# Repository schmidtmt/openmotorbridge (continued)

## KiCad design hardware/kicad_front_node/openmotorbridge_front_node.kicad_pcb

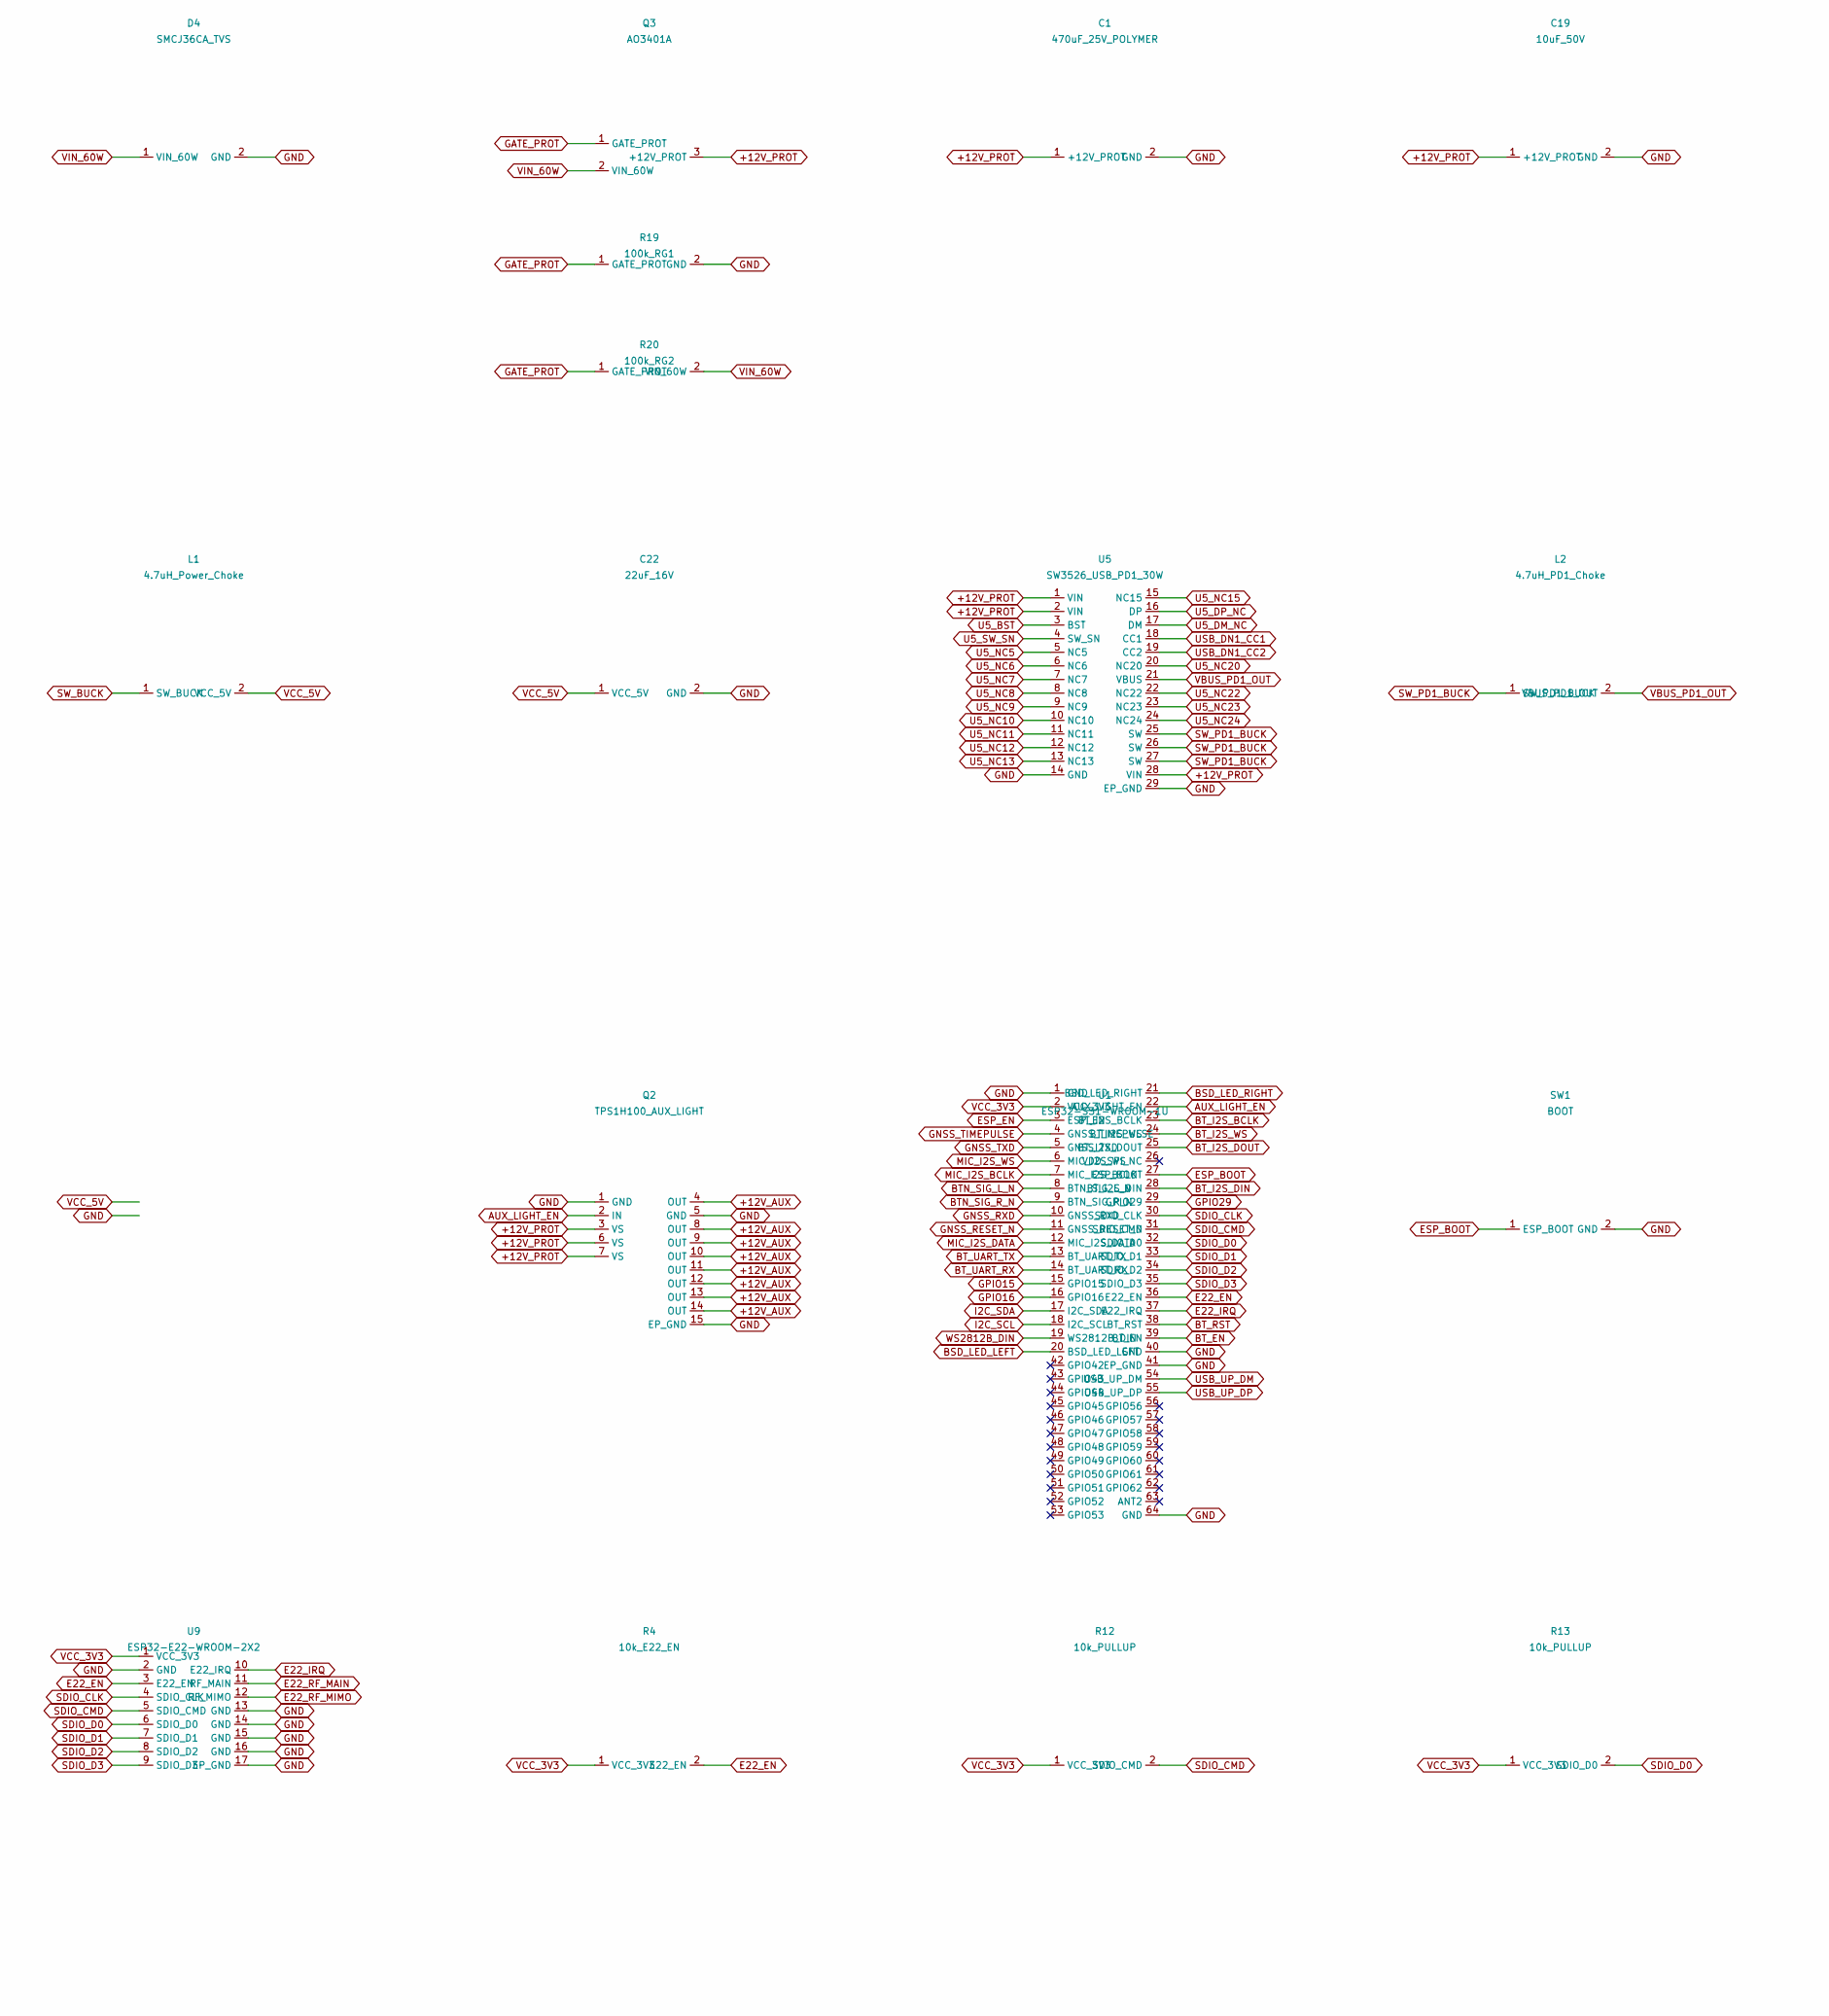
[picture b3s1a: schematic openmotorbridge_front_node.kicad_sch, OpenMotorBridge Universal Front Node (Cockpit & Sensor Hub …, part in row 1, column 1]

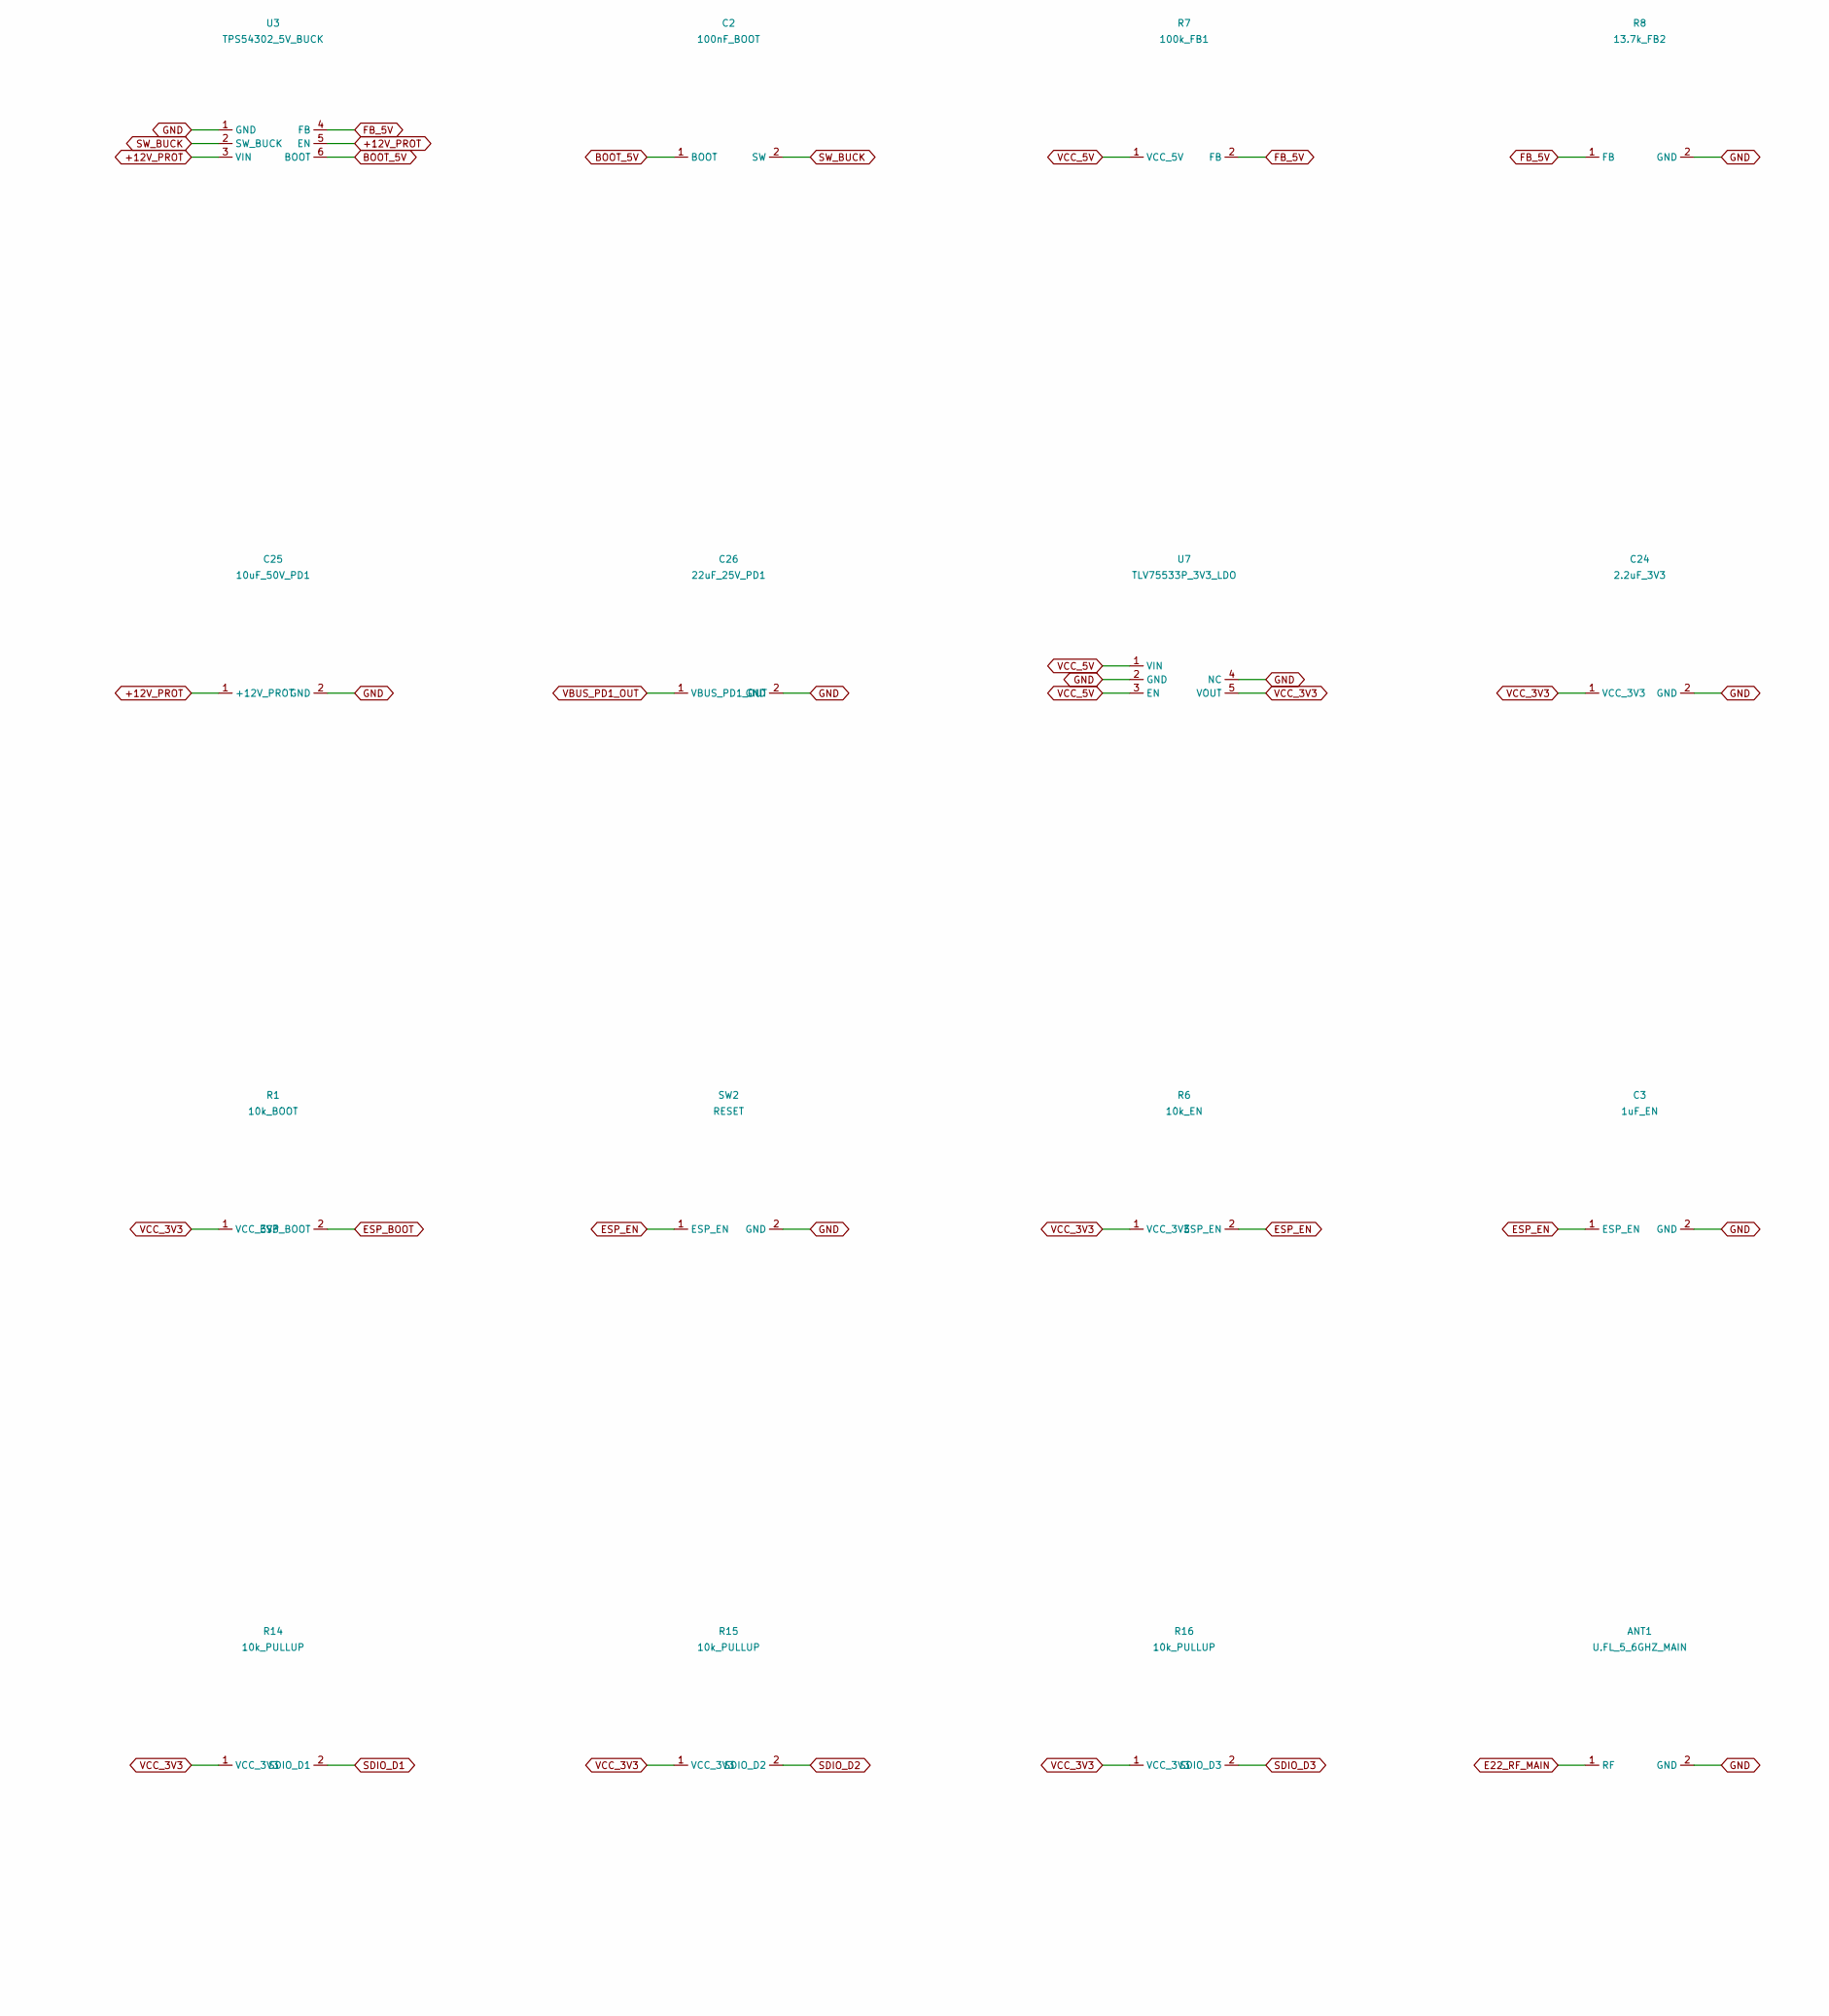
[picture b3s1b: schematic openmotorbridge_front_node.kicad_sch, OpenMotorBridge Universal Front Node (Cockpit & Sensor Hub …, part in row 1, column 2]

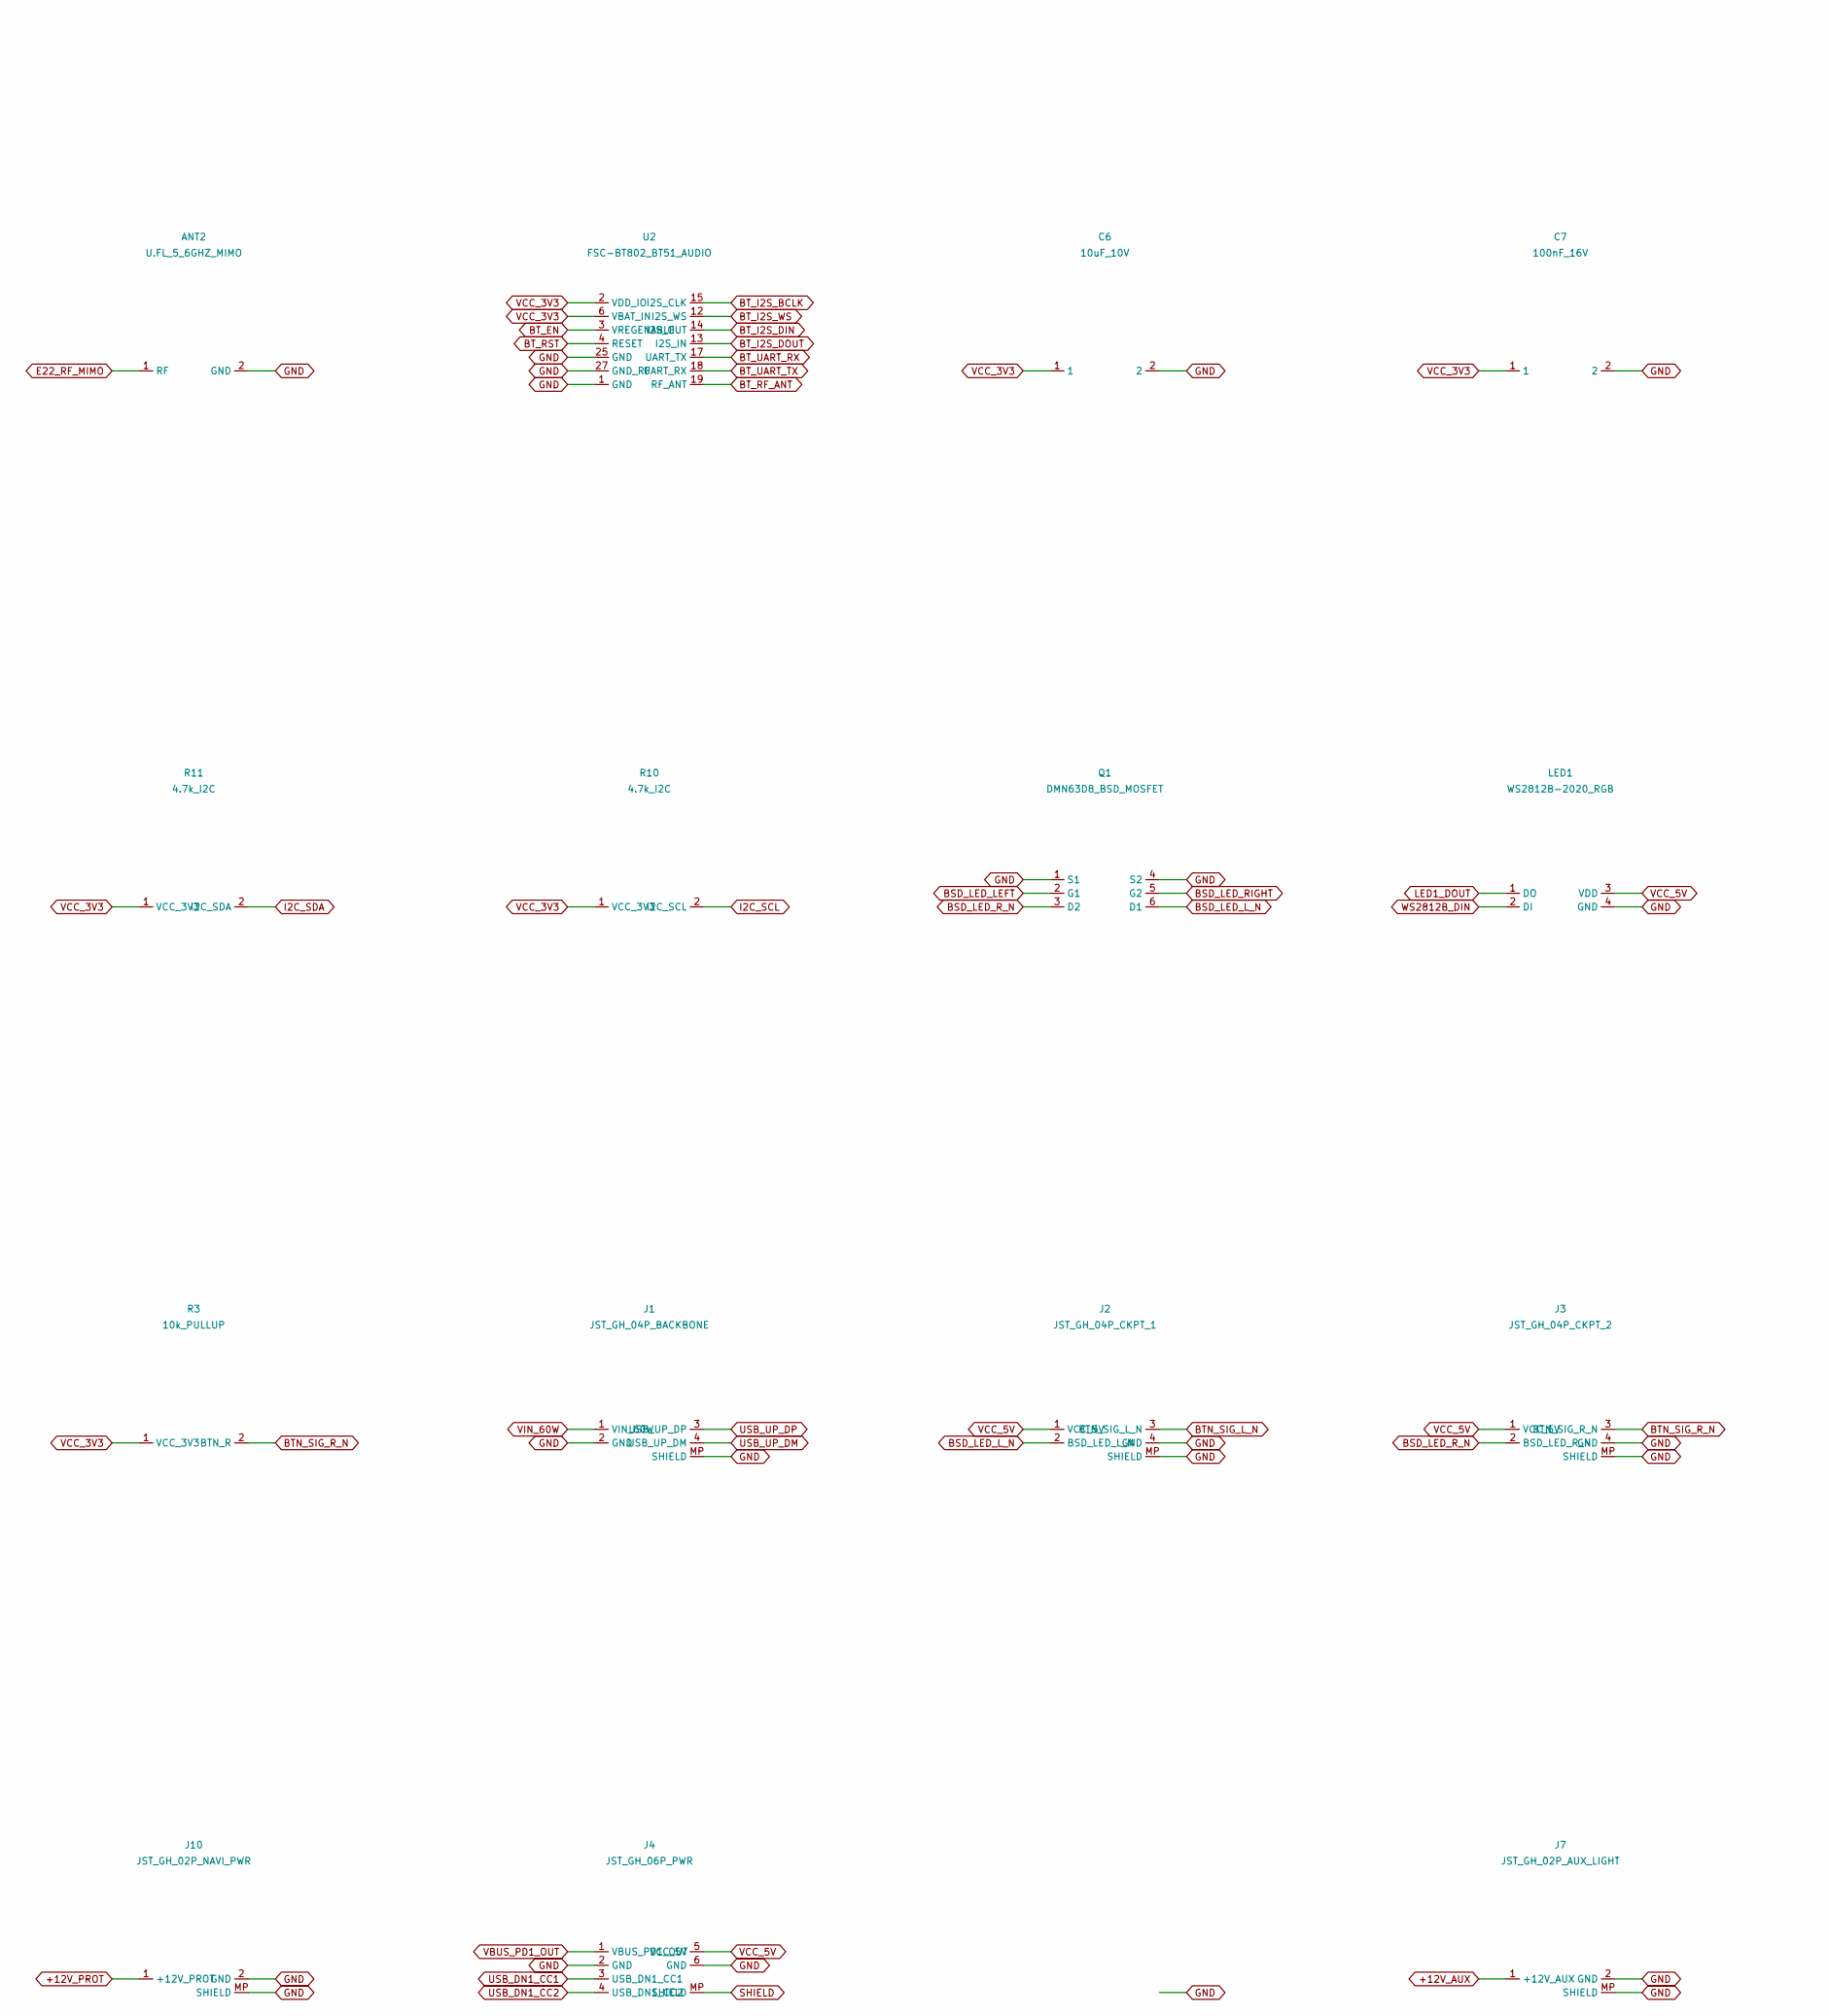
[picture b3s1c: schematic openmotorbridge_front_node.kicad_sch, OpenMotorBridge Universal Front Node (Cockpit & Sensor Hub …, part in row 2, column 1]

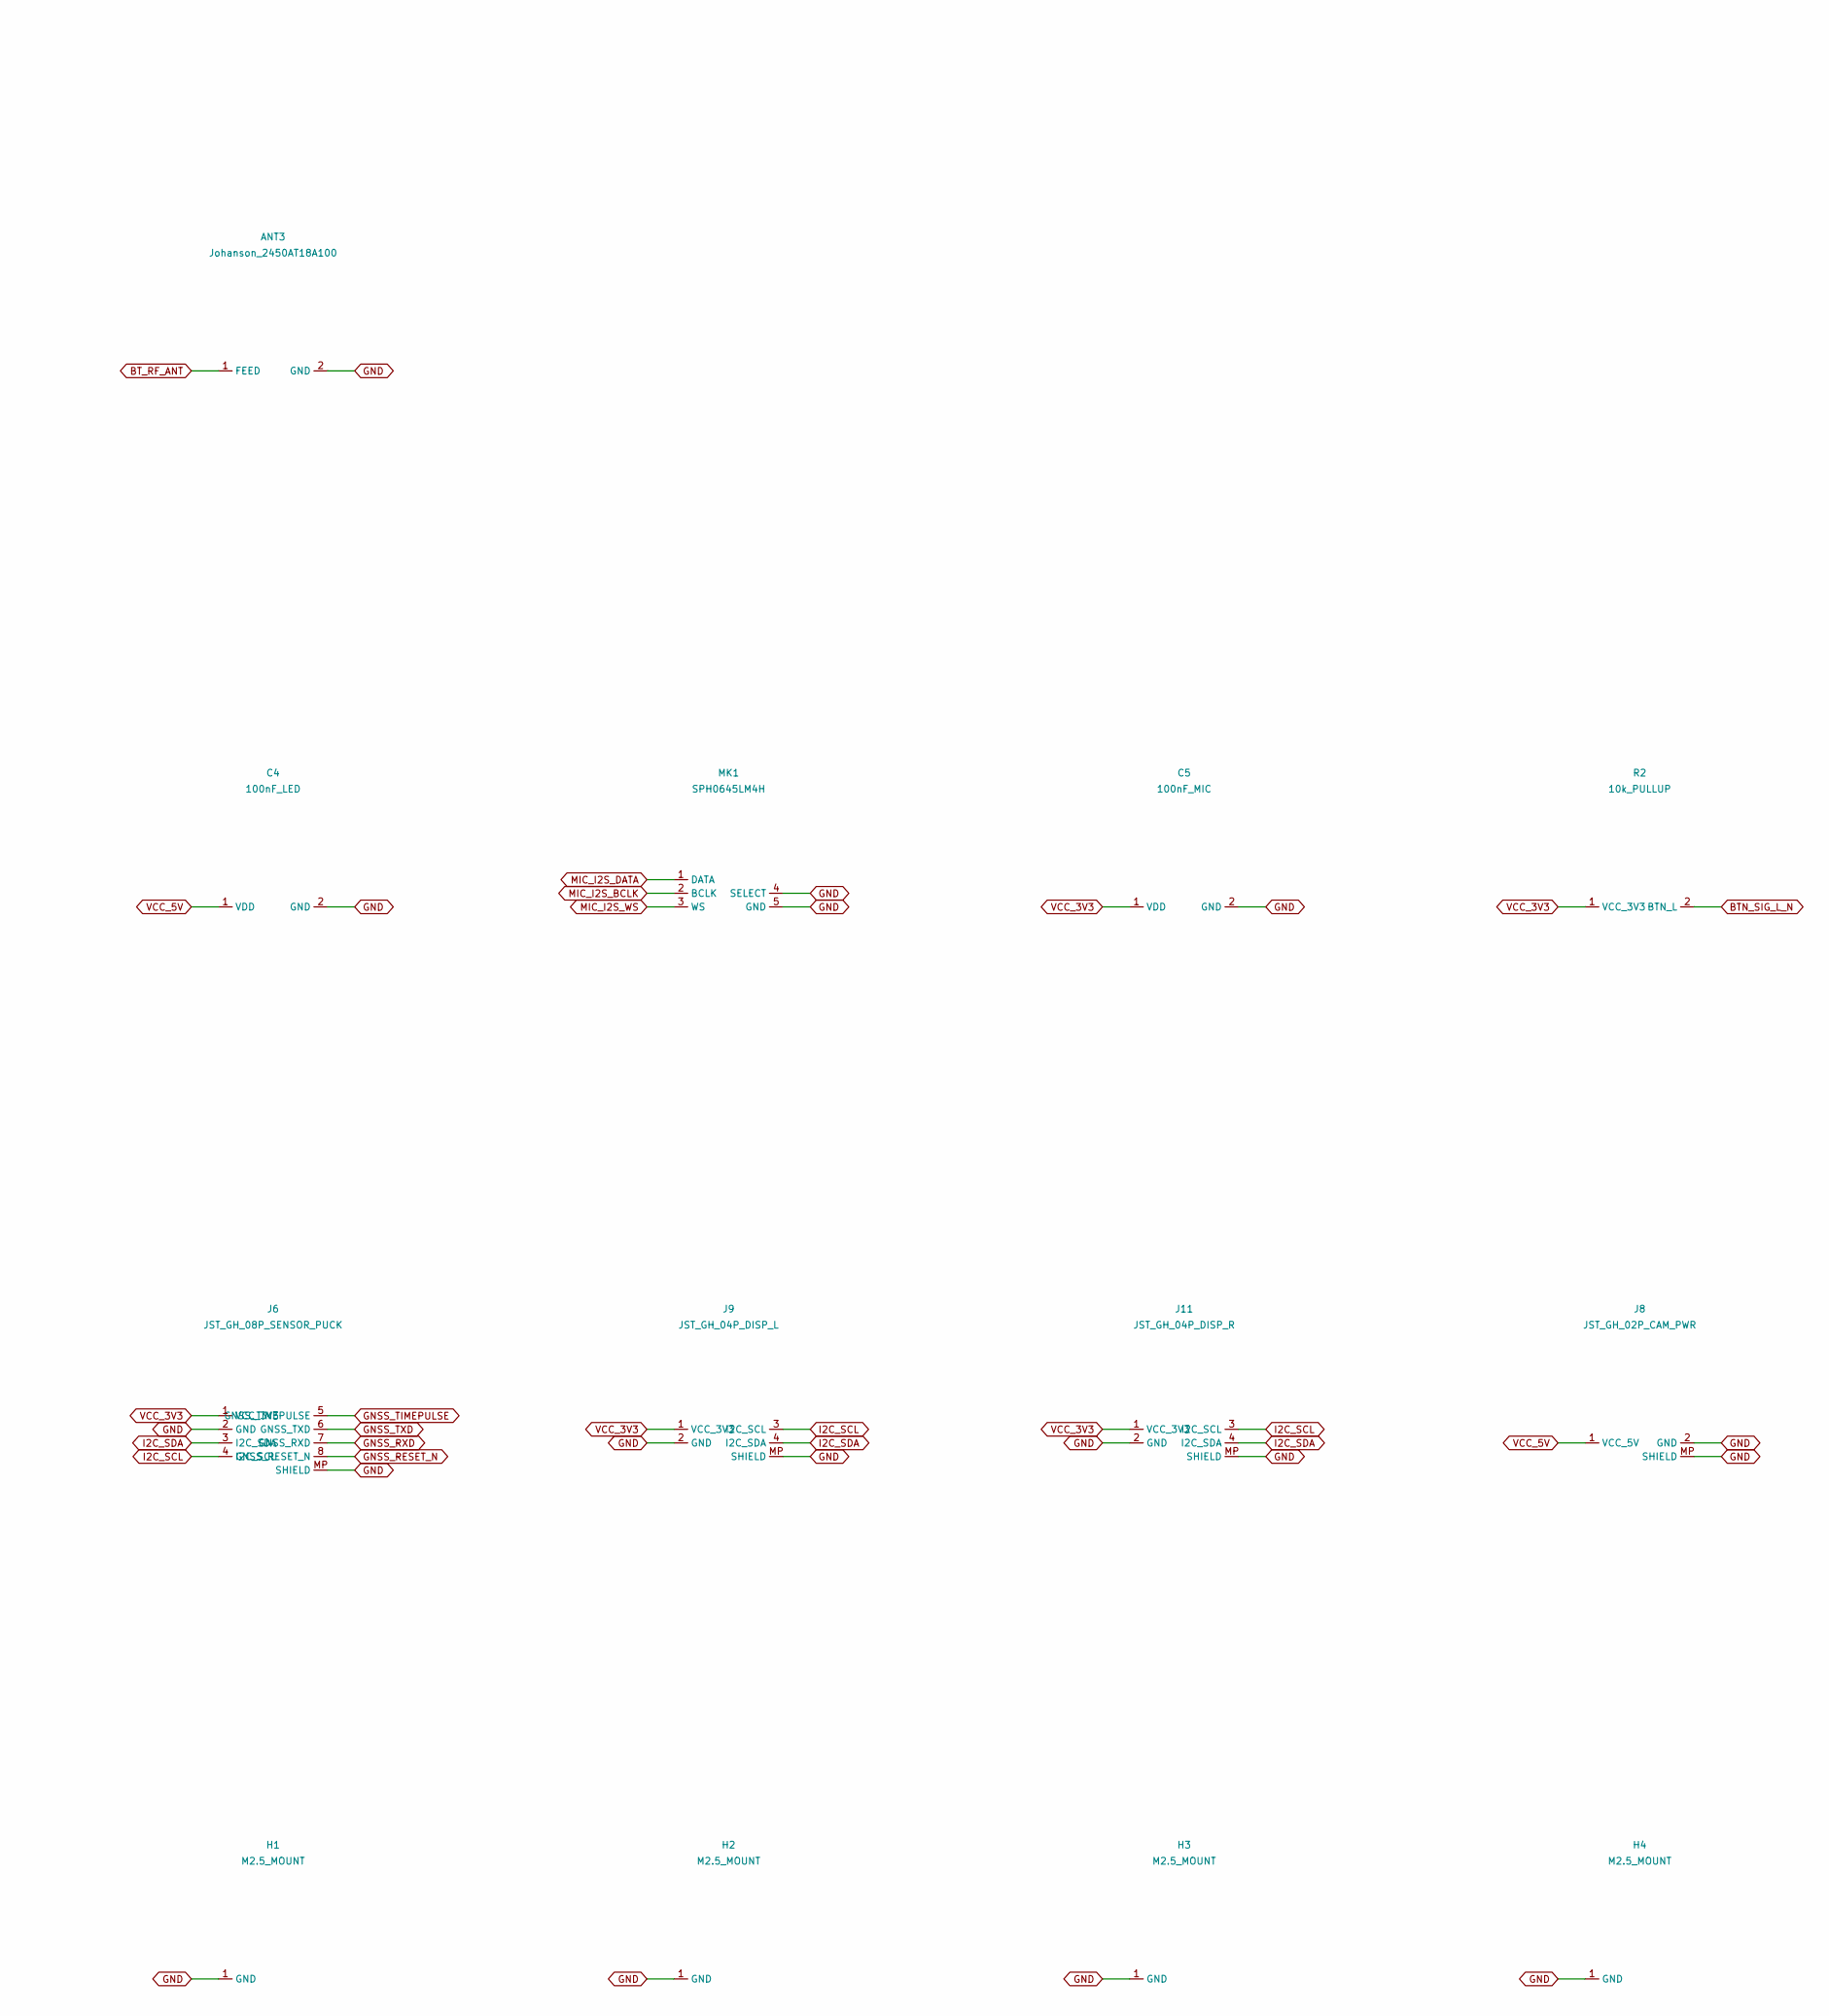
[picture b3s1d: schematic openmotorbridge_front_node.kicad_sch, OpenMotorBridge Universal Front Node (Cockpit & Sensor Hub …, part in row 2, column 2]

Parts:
ANT1: U.FL_5_6GHZ_MAIN; U.FL_Hirose_U.FL-R-SMT-1_Vertical
ANT2: U.FL_5_6GHZ_MIMO; U.FL_Hirose_U.FL-R-SMT-1_Vertical
ANT3: Johanson_2450AT18A100; Johanson_2450AT18x100
C1: 470uF_25V_POLYMER; CP_EIA-7343-31_Kemet-D
C2: 100nF_BOOT; C_0603_1608Metric
C3: 1uF_EN; C_0603_1608Metric
C4: 100nF_LED; C_0603_1608Metric
C5: 100nF_MIC; C_0603_1608Metric
C6: 10uF_10V; C_0603_1608Metric
C7: 100nF_16V; C_0603_1608Metric
C19: 10uF_50V; C_0805_2012Metric
C22: 22uF_16V; C_0805_2012Metric
C24: 2.2uF_3V3; C_0603_1608Metric
C25: 10uF_50V_PD1; C_0805_2012Metric
C26: 22uF_25V_PD1; C_0805_2012Metric
D4: SMCJ36CA_TVS; D_SMB
H1, H2, H3, H4: M2.5_MOUNT; MountingHole_2.7mm_M2.5_Pad_Via
J1: JST_GH_04P_BACKBONE; JST_GH_SM04B-GHS-TB_1x04-1MP_P1.25mm_Horizontal
J2: JST_GH_04P_CKPT_1; JST_GH_SM04B-GHS-TB_1x04-1MP_P1.25mm_Horizontal
J3: JST_GH_04P_CKPT_2; JST_GH_SM04B-GHS-TB_1x04-1MP_P1.25mm_Horizontal
J4: JST_GH_06P_PWR; JST_GH_SM06B-GHS-TB_1x06-1MP_P1.25mm_Horizontal
J6: JST_GH_08P_SENSOR_PUCK; JST_GH_SM08B-GHS-TB_1x08-1MP_P1.25mm_Horizontal
J7: JST_GH_02P_AUX_LIGHT; JST_GH_SM02B-GHS-TB_1x02-1MP_P1.25mm_Horizontal
J8: JST_GH_02P_CAM_PWR; JST_GH_SM02B-GHS-TB_1x02-1MP_P1.25mm_Horizontal
J9: JST_GH_04P_DISP_L; JST_GH_SM04B-GHS-TB_1x04-1MP_P1.25mm_Horizontal
J10: JST_GH_02P_NAVI_PWR; JST_GH_SM02B-GHS-TB_1x02-1MP_P1.25mm_Horizontal
J11: JST_GH_04P_DISP_R; JST_GH_SM04B-GHS-TB_1x04-1MP_P1.25mm_Horizontal
L1: 4.7uH_Power_Choke; L_Sunlord_MWSA1206S-470
L2: 4.7uH_PD1_Choke; L_Sunlord_MWSA0503S
LED1: WS2812B-2020_RGB; LED_WS2812B-2020_PLCC4_2.0x2.0mm
MK1: SPH0645LM4H; Knowles_SPH0645LM4H
Q1: DMN63D8_BSD_MOSFET; SOT-363_SC-70-6
Q2: TPS1H100_AUX_LIGHT; Texas_HTSSOP-14-1EP_4.4x5mm_P0.65mm_EP3.4x5mm_Mask3.155x3.2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
Q3: AO3401A; SOT-23
R1: 10k_BOOT; R_0603_1608Metric
R2, R3, R12, R13, R14, R15, R16: 10k_PULLUP; R_0603_1608Metric
R4: 10k_E22_EN; R_0603_1608Metric
R6: 10k_EN; R_0603_1608Metric
R7: 100k_FB1; R_0603_1608Metric
R8: 13.7k_FB2; R_0603_1608Metric
R10, R11: 4.7k_I2C; R_0603_1608Metric
R19: 100k_RG1; R_0402_1005Metric
R20: 100k_RG2; R_0402_1005Metric
SW1: BOOT; SW_Push_SPST_NO_Alps_SKRK
SW2: RESET; SW_Push_SPST_NO_Alps_SKRK
U1: ESP32-S31-WROOM-1U
U2: FSC-BT802_BT51_AUDIO; Feasycom_FSC-BT802
U3: TPS54302_5V_BUCK; SOT-23-6
U5: SW3526_USB_PD1_30W; QFN-28-1EP_4x4mm_P0.4mm_EP2.4x2.4mm_ThermalVias
U7: TLV75533P_3V3_LDO; SOT-23-5
U9: ESP32-E22-WROOM-2X2; QFN-16-1EP_3x3mm_P0.5mm_EP1.7x1.7mm_ThermalVias

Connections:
+12V_AUX: J7.1 (+12V_AUX), Q2.4 (OUT), Q2.8 (OUT), Q2.9 (OUT), Q2.10 (OUT), Q2.11 (OUT), Q2.12 (OUT), Q2.13 (OUT), Q2.14 (OUT)
+12V_PROT: C1.1 (+12V_PROT), C19.1 (+12V_PROT), C25.1 (+12V_PROT), J10.1 (+12V_PROT), Q2.3 (VS), Q2.6 (VS), Q2.7 (VS), Q3.3 (ACT_2), U3.3 (VIN), U3.5 (EN), U5.1 (VIN), U5.2 (VIN), U5.28 (VIN)
AUX_LIGHT_EN: Q2.2 (IN), U1.22 (AUX_LIGHT_EN)
BOOT_5V: C2.1 (BOOT), U3.6 (BOOT)
BSD_LED_LEFT: Q1.2 (G1), U1.20 (BSD_LED_LEFT)
BSD_LED_L_N: J2.2 (BSD_LED_L_N), Q1.6 (D1)
BSD_LED_RIGHT: Q1.5 (G2), U1.21 (BSD_LED_RIGHT)
BSD_LED_R_N: J3.2 (BSD_LED_R_N), Q1.3 (D2)
BTN_SIG_L_N: J2.3 (BTN_SIG_L_N), R2.2 (BTN_L), U1.8 (BTN_SIG_L_N)
BTN_SIG_R_N: J3.3 (BTN_SIG_R_N), R3.2 (BTN_R), U1.9 (BTN_SIG_R_N)
BT_EN: U1.39 (CP2AA_PWR_EN), U2.3
BT_I2S_BCLK: U1.23 (GPIO23), U2.15
BT_I2S_DIN: U1.28 (GPIO28), U2.14
BT_I2S_DOUT: U1.25 (GPIO25), U2.13
BT_I2S_WS: U1.24 (GPIO24), U2.12
BT_RF_ANT: ANT3.1 (FEED), U2.19
BT_RST: U1.38 (CP2AA_FAULT_N), U2.4
BT_UART_RX: U1.14 (GPIO34), U2.17
BT_UART_TX: U1.13 (GPIO33), U2.18
E22_EN: R4.2 (E22_EN), U1.36 (E22_EN), U9.3 (E22_EN)
E22_IRQ: U1.37 (E22_IRQ), U9.10 (E22_IRQ)
E22_RF_MAIN: ANT1.1 (RF), U9.11 (RF_MAIN)
E22_RF_MIMO: ANT2.1 (RF), U9.12 (RF_MIMO)
ESP_BOOT: R1.2 (ESP_BOOT), SW1.1 (ESP_BOOT), U1.27 (ESP_BOOT)
ESP_EN: C3.1 (ESP_EN), R6.2 (ESP_EN), SW2.1 (ESP_EN), U1.3 (ESP_EN)
FB_5V: R7.2 (FB), R8.1 (FB), U3.4 (FB)
GATE_PROT: Q3.1 (Q2_GATE), R19.1 (VCC_3V3), R20.1 (VCC_3V3)
GND: ANT1.2 (GND), ANT2.2 (GND), ANT3.2 (GND), C1.2 (GND), C3.2 (GND), C4.2 (GND), C5.2 (GND), C6.2 (GND), C7.2 (GND), C19.2 (GND), C22.2 (GND), C24.2 (GND), C25.2 (GND), C26.2 (GND), D4.2 (GND), H1.1 (GND), H2.1 (GND), H3.1 (GND), H4.1 (GND), J1.2 (GND), J1.MP (SHIELD), J2.4 (GND), J2.MP (SHIELD), J3.4 (GND), J3.MP (SHIELD), J4.2 (GND), J4.6 (GND), J6.2 (GND), J6.MP (SHIELD), J7.2 (GND), J7.MP (SHIELD), J8.2 (GND), J8.MP (SHIELD), J9.2 (GND), J9.MP (SHIELD), J10.2 (GND), J10.MP (SHIELD), J11.2 (GND), J11.MP (SHIELD), LED1.4 (GND), MK1.4 (SELECT), MK1.5 (GND), Q1.1 (S1), Q1.4 (S2), Q2.1 (GND), Q2.5 (GND), Q2.15 (EP_GND), R8.2 (GND), R19.2 (BTN_SOS_N), SW1.2 (GND), SW2.2 (GND), U1.1 (GND), U1.40 (GND), U1.41 (EP_GND), U1.64 (GND), U2.1, U2.25, U2.27, U3.1 (GND), U5.14 (GND), U5.29 (EP_GND), U7.2 (GND), U7.4 (NC), U9.2 (GND), U9.13 (GND), U9.14 (GND), U9.15 (GND), U9.16 (GND), U9.17 (EP_GND)
GNSS_RESET_N: J6.8 (GNSS_RESET_N), U1.11 (GNSS_RESET_N)
GNSS_RXD: J6.7 (GNSS_RXD), U1.10 (GNSS_RXD)
GNSS_TIMEPULSE: J6.5 (GNSS_TIMEPULSE), U1.4 (GNSS_TIMEPULSE)
GNSS_TXD: J6.6 (GNSS_TXD), U1.5 (GNSS_TXD)
GPIO15: U1.15 (GPIO15)
GPIO16: U1.16 (GPIO16)
GPIO29: U1.29 (GPIO29)
I2C_SCL: J6.4 (I2C_SCL), J9.3 (I2C_SCL), J11.3 (I2C_SCL), R10.2 (I2C_SCL), U1.18 (I2C_SCL)
I2C_SDA: J6.3 (I2C_SDA), J9.4 (I2C_SDA), J11.4 (I2C_SDA), R11.2 (I2C_SDA), U1.17 (I2C_SDA)
LED1_DOUT: LED1.1 (DO)
MIC_I2S_BCLK: MK1.2 (BCLK), U1.7 (MIC_I2S_BCLK)
MIC_I2S_DATA: MK1.1 (DATA), U1.12 (MIC_I2S_DATA)
MIC_I2S_WS: MK1.3 (WS), U1.6 (MIC_I2S_WS)
SDIO_CLK: U1.30 (SDIO_CLK), U9.4 (SDIO_CLK)
SDIO_CMD: R12.2 (SDIO_CMD), U1.31 (SDIO_CMD), U9.5 (SDIO_CMD)
SDIO_D0: R13.2 (SDIO_D0), U1.32 (SDIO_D0), U9.6 (SDIO_D0)
SDIO_D1: R14.2 (SDIO_D1), U1.33 (SDIO_D1), U9.7 (SDIO_D1)
SDIO_D2: R15.2 (SDIO_D2), U1.34 (SDIO_D2), U9.8 (SDIO_D2)
SDIO_D3: R16.2 (SDIO_D3), U1.35 (SDIO_D3), U9.9 (SDIO_D3)
SHIELD: J4.MP (SHIELD)
SW_BUCK: C2.2 (SW), L1.1 (SW_BUCK), U3.2 (SW_BUCK)
SW_PD1_BUCK: L2.1 (SW_PD1_BUCK), U5.25 (SW), U5.26 (SW), U5.27 (SW)
U5_BST: U5.3 (BST)
U5_DM_NC: U5.17 (DM)
U5_DP_NC: U5.16 (DP)
U5_NC5: U5.5 (NC5)
U5_NC6: U5.6 (NC6)
U5_NC7: U5.7 (NC7)
U5_NC8: U5.8 (NC8)
U5_NC9: U5.9 (NC9)
U5_NC10: U5.10 (NC10)
U5_NC11: U5.11 (NC11)
U5_NC12: U5.12 (NC12)
U5_NC13: U5.13 (NC13)
U5_NC15: U5.15 (NC15)
U5_NC20: U5.20 (NC20)
U5_NC22: U5.22 (NC22)
U5_NC23: U5.23 (NC23)
U5_NC24: U5.24 (NC24)
U5_SW_SN: U5.4 (SW_SN)
USB_DN1_CC1: J4.3 (USB_DN1_CC1), U5.18 (CC1)
USB_DN1_CC2: J4.4 (USB_DN1_CC2), U5.19 (CC2)
USB_UP_DM: J1.4 (USB_UP_DM), U1.54 (USB_HS_DM)
USB_UP_DP: J1.3 (USB_UP_DP), U1.55 (USB_HS_DP)
VBUS_PD1_OUT: C26.1 (VBUS_PD1_OUT), J4.1 (VBUS_PD1_OUT), L2.2 (VBUS_PD1_OUT), U5.21 (VBUS)
VCC_3V3: C5.1 (VDD), C6.1 (VDD18), C7.1 (XTAL_IN), C24.1 (VCC_3V3), J6.1 (VCC_3V3), J9.1 (VCC_3V3), J11.1 (VCC_3V3), R1.1 (VCC_3V3), R2.1 (VCC_3V3), R3.1 (VCC_3V3), R4.1 (VCC_3V3), R6.1 (VCC_3V3), R10.1 (VCC_3V3), R11.1 (VCC_3V3), R12.1 (VCC_3V3), R13.1 (VCC_3V3), R14.1 (VCC_3V3), R15.1 (VCC_3V3), R16.1 (VCC_3V3), U1.2 (VCC_3V3), U2.2, U2.6, U7.5 (VOUT), U9.1 (VCC_3V3)
VCC_5V: C4.1 (VDD), C22.1 (VCC_5V), J2.1 (VCC_5V), J3.1 (VCC_5V), J4.5 (VCC_5V), J8.1 (VCC_5V), L1.2 (VCC_5V), LED1.3 (VDD), R7.1 (VCC_5V), U7.1 (VIN), U7.3 (EN)
VIN_60W: D4.1 (VIN_60W), J1.1 (VIN_60W), Q3.2 (GND), R20.2 (BTN_SOS_N)
WS2812B_DIN: LED1.2 (DI), U1.19 (WS2812B_DIN)

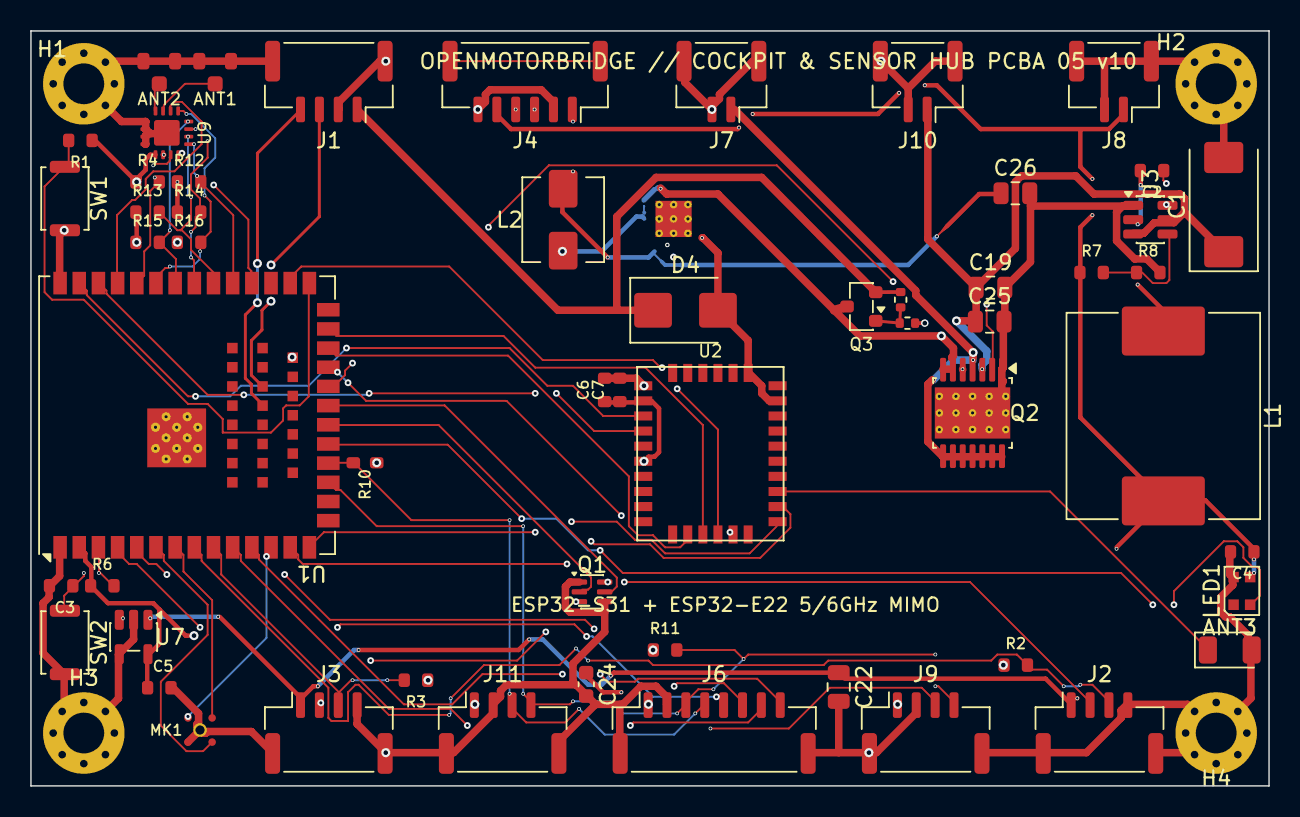
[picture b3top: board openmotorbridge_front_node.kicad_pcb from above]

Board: 4 copper layers, 82.0 x 50.0 mm, 61 parts (1 on the bottom side), 54 nets.
